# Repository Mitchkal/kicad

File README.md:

# kicad
A repo of my kicad pcb projects

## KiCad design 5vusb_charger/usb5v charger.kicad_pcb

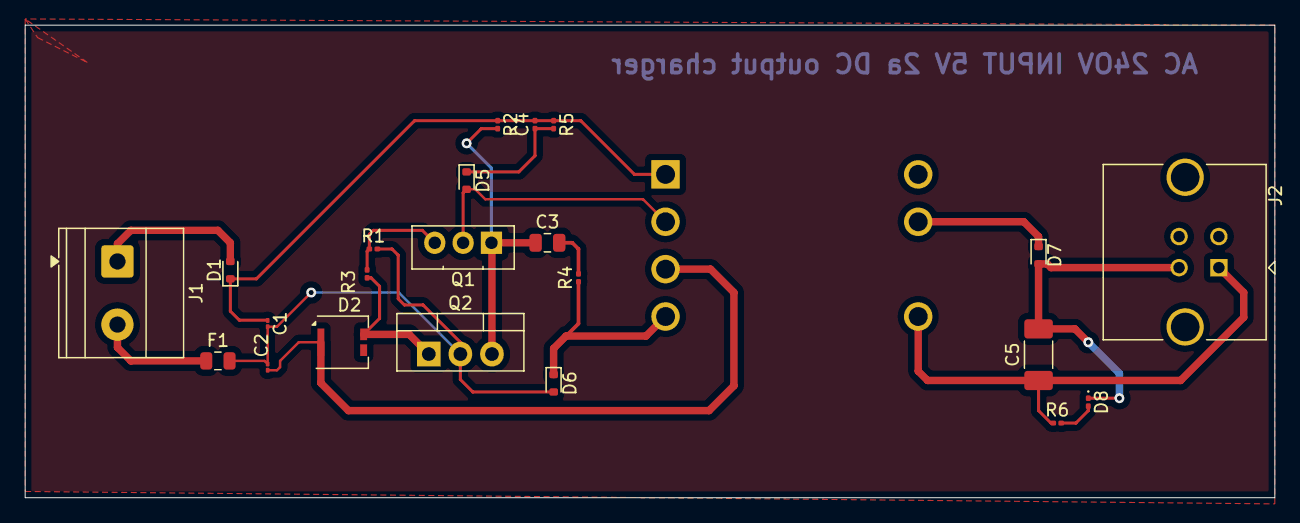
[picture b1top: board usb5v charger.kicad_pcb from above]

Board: 2 copper layers, 100.5 x 38.0 mm, 23 parts (1 on the bottom side), 16 nets.

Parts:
C1: C_Polarized_US; C_01005_0402Metric
C2: 22uF; C_01005_0402Metric
C3: 472; C_0805_2012Metric
C4: 103/1KV; C_0201_0603Metric
C5: 220uF; C_1808_4520Metric
D1, D5, D6, D7: 1N4148WT; D_SOD-523
D2: D_Zener; Littelfuse_PolyZen-LS
D8: LED; LED_0201_0603Metric
F1: Fuse_Small; Fuse_0805_2012Metric
J1: Conn_01x02_Pin; TerminalBlock_Phoenix_MKDS-1,5-2-5.08_1x02_P5.08mm_Horizont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
J2: USB_B; USB_B_TE_5787834_Vertical
Q1: MJE13003; TO-126-3_Vertical
Q2: 2SC1945; TO-220-3_Vertical
R1: 13; R_0201_0603Metric
R2: 1M5; R_0201_0603Metric
R3: 100; R_0201_0603Metric
R4, R6: 1K; R_0201_0603Metric
R5: 47K; R_0201_0603Metric
T1: LL1587; Transformer_Microphone_Lundahl_LL1587

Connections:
unnamed: C3.2, R4.2
unnamed: D1.2 (A), J1.1
unnamed: C1.1, C4.2, D1.1 (K), R2.1, R5.1, T1.1 (P1+)
unnamed: D2.2 (A), Q2.1 (B), R3.1
unnamed: C2.1, D2.1 (K), T1.3 (P2-)
unnamed: D5.2 (A), Q1.2 (C), T1.2 (P1-)
unnamed: C4.1, D5.1 (K), R5.2
unnamed: C1.2, C2.2, D6.2 (A), F1.2, Q2.2 (E), R1.2
unnamed: D6.1 (K), R4.1, T1.4 (P2+)
unnamed: C5.2, D7.2 (A), D8.1 (K), J2.4 (GND)
unnamed: D7.1 (K), T1.6 (S-)
unnamed: D8.2 (A), R6.2
unnamed: F1.1, J1.2
unnamed: C5.1, J2.1 (VBUS), R6.1, T1.8 (S+)
unnamed: C3.1, Q1.1 (B), Q2.3 (C), R2.2
unnamed: Q1.3 (E), R1.1, R3.2

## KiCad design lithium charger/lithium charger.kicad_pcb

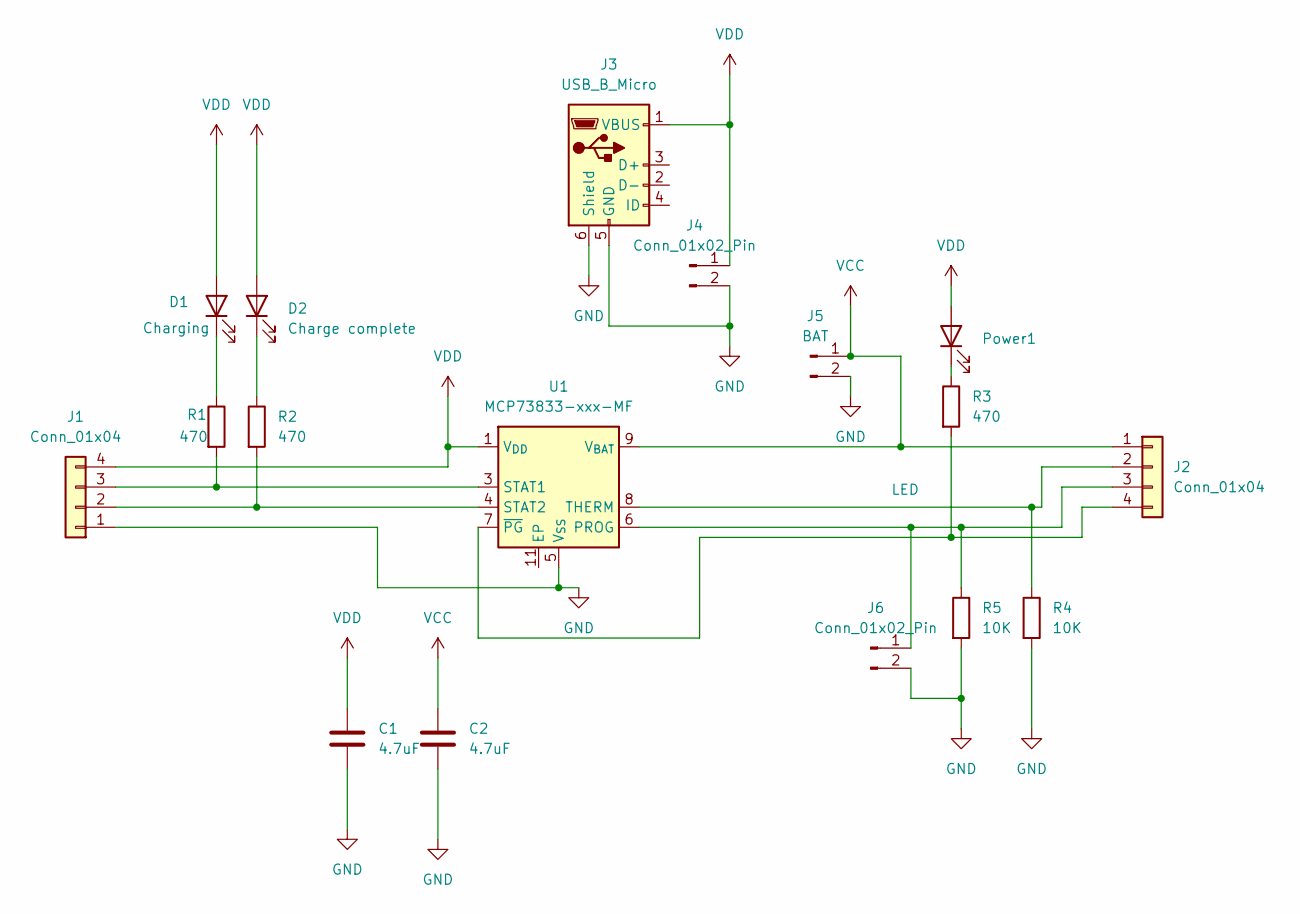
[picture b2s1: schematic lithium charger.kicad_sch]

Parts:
C1, C2: 4.7uF; C_0201_0603Metric_Pad0.64x0.40mm_HandSolder
D1: Charging; LED_0201_0603Metric
D2: Charge complete; LED_0201_0603Metric
J1: Conn_01x04; FanPinHeader_1x04_P2.54mm_Vertical
J2: Conn_01x04; Hirose_DF57H-4P-1.2V_1x04_P1.2mm_Socket
J3: USB_B_Micro; USB_Micro-AB_Molex_47590-0001
J4: Conn_01x02_Pin; JWT_A3963_1x02_P3.96mm_Vertical
J5: BAT; Jumper_Harwin_S1621_P10.9mm
J6: Conn_01x02_Pin; Jumper_Harwin_S1621_P10.9mm
Power1: LED; LED_0603_1608Metric_Pad1.05x0.95mm_HandSolder
R1: 470; R_0603_1608Metric
R2, R3: 470; R_0201_0603Metric_Pad0.64x0.40mm_HandSolder
R4, R5: 10K; R_0201_0603Metric_Pad0.64x0.40mm_HandSolder
U1: MCP73833-xxx-MF; DFN-10-1EP_3x3mm_P0.5mm_EP1.58x2.35mm

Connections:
GND: C1.2, C2.2, J1.1, J3.5 (GND), J3.6 (Shield), J4.2, J5.2, J6.2, R4.2, R5.2, U1.5 (V_{SS})
unnamed: D1.1 (K), R1.1
unnamed: D2.1 (K), R2.1
unnamed: J1.2, R2.2, U1.4 (STAT2)
unnamed: J1.3, R1.2, U1.3 (STAT1)
unnamed: J2.2, R4.1, U1.8 (THERM)
unnamed: J2.3, J6.1, R5.1, U1.6 (PROG)
unnamed: J2.4, R3.2, U1.7 (~PG)
unnamed: Power1.1 (K), R3.1
VCC: C2.1, J2.1, J5.1, U1.9 (V_{BAT}), U1.10 (V_{BAT})
VDD: C1.1, D1.2 (A), D2.2 (A), J1.4, J3.1 (VBUS), J4.1, Power1.2 (A), U1.1 (V_{DD}), U1.2 (V_{DD})

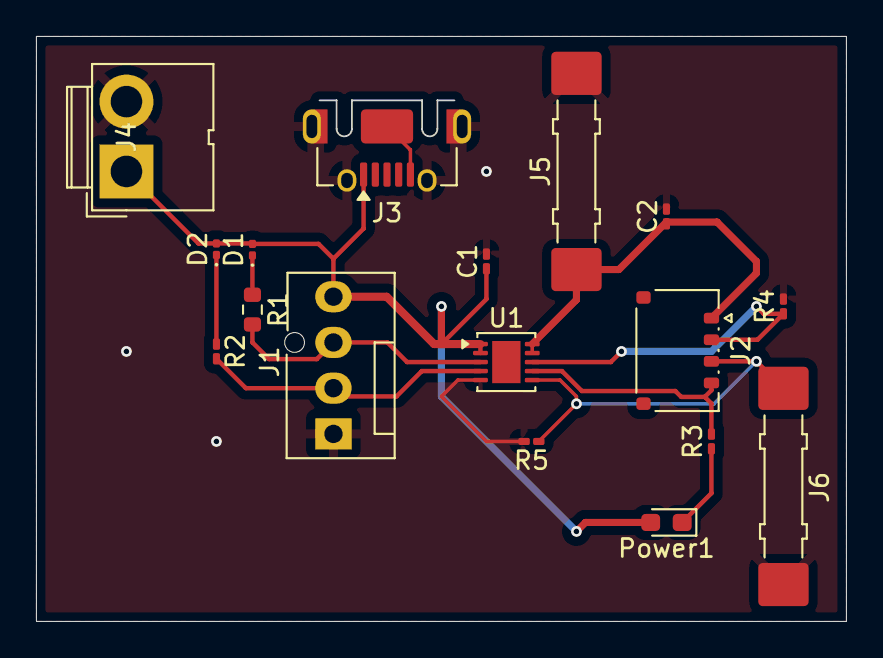
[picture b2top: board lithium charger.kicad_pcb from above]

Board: 2 copper layers, 45.0 x 32.5 mm, 17 parts (0 on the bottom side), 11 nets.

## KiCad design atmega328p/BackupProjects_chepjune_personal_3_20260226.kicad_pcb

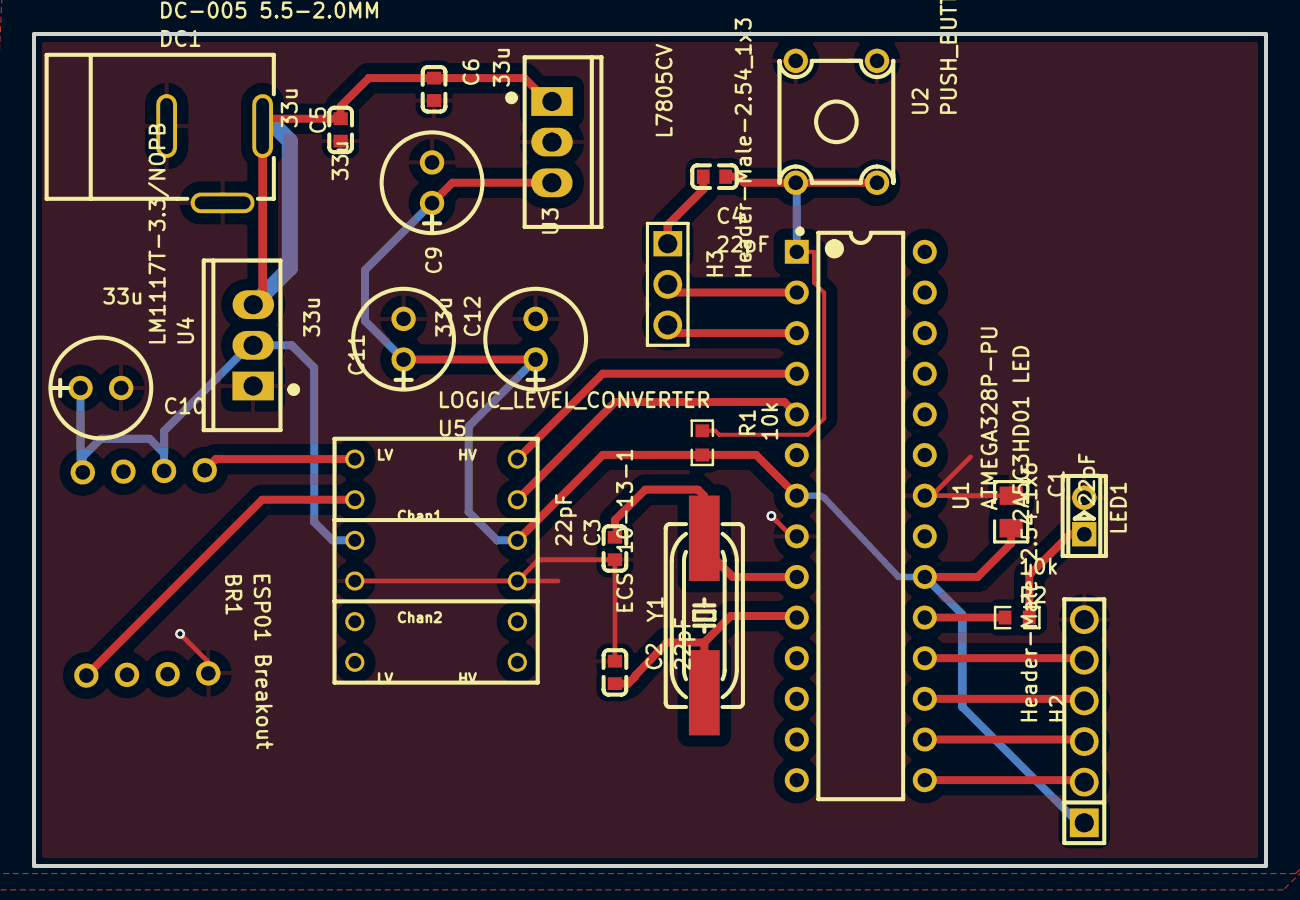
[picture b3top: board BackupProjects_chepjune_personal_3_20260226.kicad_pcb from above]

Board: 2 copper layers, 77.0 x 52.0 mm, 23 parts (0 on the bottom side), 20 nets.

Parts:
BR1: ESP01 Breakout; ESP01 BREAKOUT
C1: 22pF; 0805
C2, C3, C4: 22pF; C0603
C5, C6: 33u; C0603
C9, C10, C11, C12: 33u; CAP-D6.3XF2.5
DC1: DC-005 5.5-2.0MM; DC-IN-TH_DC-5520-1
H2: Header-Male-2.54_1x6; HDR-TH_6P-P2.54-V-M-1
H3: Header-Male-2.54_1x3; HDR-TH_3P-P2.54-V-M-1
LED1: 2A5G3HD01 LED; LED-SMD_L5.0-W2.7-FD
R1, R2: 10k; R0603
U1: ATMEGA328P-PU; DIP-28_L34.6-W7.3-P2.54-LS10.2-BL
U2: PUSH_BUTTON
U3: L7805CV; TO-220-3_L10.0-W4.5-P2.54-L
U4: LM1117T-3.3/NOPB; TO-220-3_L10.0-W4.5-P2.54-L
U5: LOGIC_LEVEL_CONVERTER
Y1: ECS-10-13-1; HC-49U

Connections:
GND: BR1.5, C1.1, C2.1, C3.1, C5.1, C6.2, C9.2, C10.2, C11.2, C12.2, DC1.2, DC1.3, H2.6, LED1.2, U1.8, U1.22, U2.1, U2.2, U3.2, U4.1, U5.P$4, U5.P$9
H3_1: C4.2, H3.1
LED1_1: LED1.1, R2.2
U1_1: C4.1, R1.1, U1.1, U2.3, U2.4
U1_2: H3.2, U1.2
U1_3: H3.3, U1.3
U1_4: U1.4, U5.P$12
U1_5: U1.5, U5.P$11
U1_7: C1.2, C9.1, C11.1, C12.1, H2.1, R1.2, U1.7, U1.20, U3.3, U5.P$10
U1_9: C3.2, U1.9, Y1.2
U1_10: C2.2, U1.10, Y1.1
U1_15: H2.2, U1.15
U1_16: H2.3, U1.16
U1_17: H2.4, U1.17
U1_18: H2.5, U1.18
U1_19: R2.1, U1.19
U3_1: C5.2, C6.1, DC1.4, U3.1, U4.3
U4_2: BR1.2, BR1.4, C10.1, U4.2, U5.P$3
U5_P$1: BR1.1, U5.P$1
U5_P$2: BR1.8, U5.P$2
